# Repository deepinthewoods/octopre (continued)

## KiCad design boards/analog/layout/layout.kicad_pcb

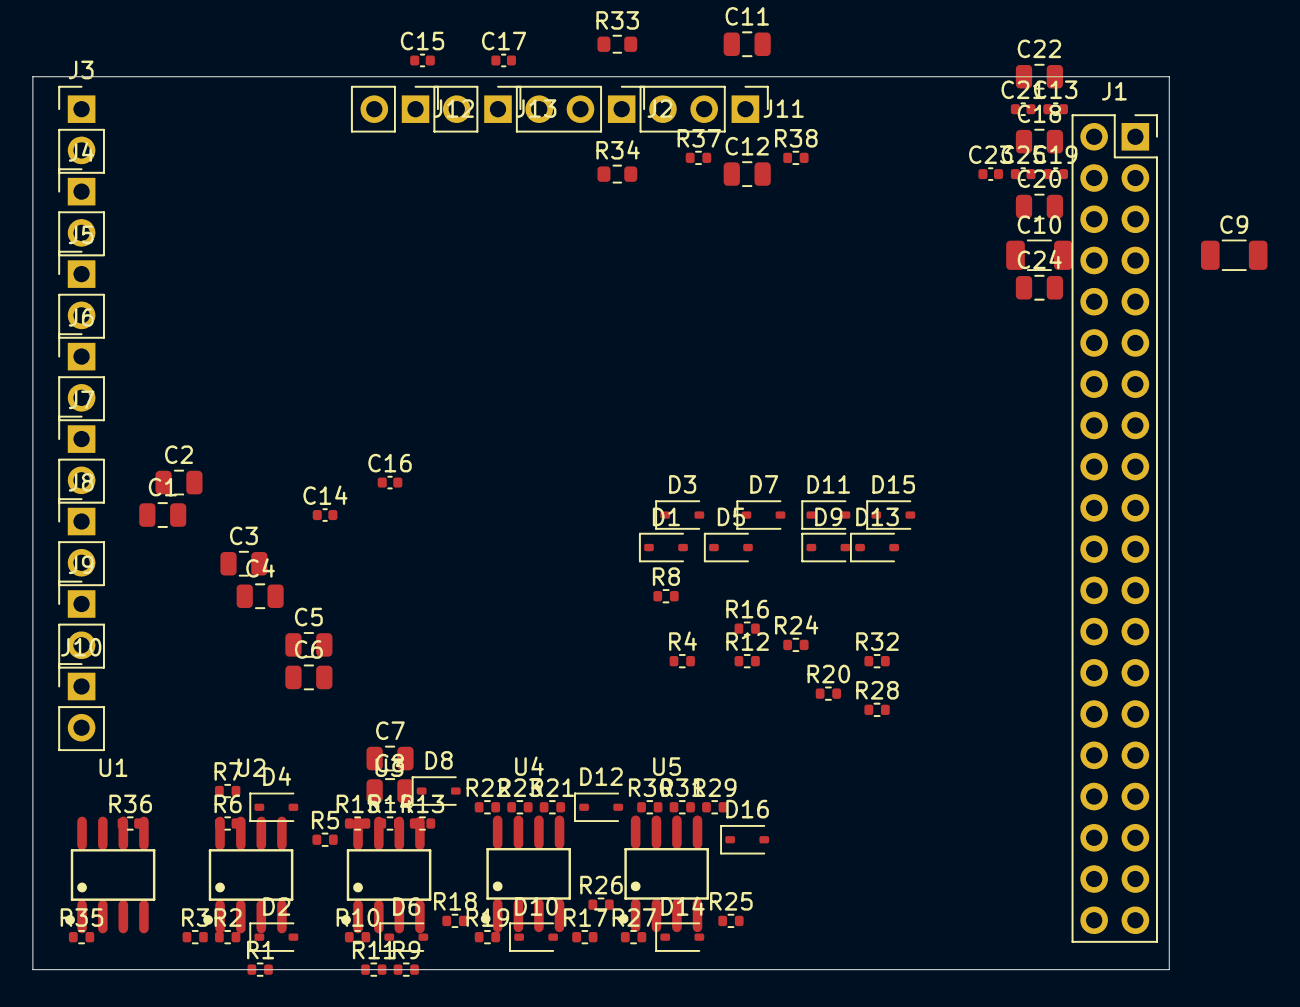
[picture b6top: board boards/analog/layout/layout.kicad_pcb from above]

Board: 6 copper layers, 70.0 x 55.0 mm, 97 parts (0 on the bottom side), 60 nets, no tracks yet.

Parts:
C1, C2, C3, C4, C5, C6, C7, C8, C11, C12, C18, C20, C22, C24: GRM21BZ71E106KE15K; C_0805_2012Metric
C9, C10: 220uF; C_1206_3216Metric
C13, C15, C17, C19, C21, C23, C25: GCM155R71H104KE02D; C_0402_1005Metric
C14, C16: GRM155Z71A105KE01D; C_0402_1005Metric
D1, D2, D3, D4, D5, D6, D7, D8, D9, D10, D11, D12, D13, D14, D15, D16: Schottky; D_SOD-323
J1: 2.54mm 20 x 2 THT Vertical Female; PinSocket_2x20_P2.54mm_Vertical
J2, J11: 61300311121; PinHeader_1x03_P2.54mm_Vertical
J3, J4, J5, J6, J7, J8, J9, J10, J12, J13: 61300211121; PinHeader_1x02_P2.54mm_Vertical
R1, R5, R9, R13, R17, R21, R25, R29: ERJ-2RKF1003X; R_0402_1005Metric
R2, R6, R10, R14, R18, R22, R26, R30: ERJ-2RKF1002X; R_0402_1005Metric
R3, R7, R11, R15, R19, R23, R27, R31: ERJ-2RKF1001X; R_0402_1005Metric
R4, R8, R12, R16, R20, R24, R28, R32: ERJ-2RKF1000X; R_0402_1005Metric
R33, R34: ERJ-H3QF1R0V; R_0603_1608Metric
R35, R36: 600; R_0402_1005Metric
R37, R38: ERJ-2RKF2201X; R_0402_1005Metric
U1, U2, U3, U4, U5: OPA2134UA

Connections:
3V3_ANA: C13.1, C18.1, C19.1, C20.1, C21.1, C22.1, C23.1, C24.1, C25.1, D1.1, D3.1, D5.1, D7.1, D9.1, D11.1, D13.1, D15.1, J1.4, J1.5, R37.1, R38.1, U1.8, U2.8, U3.8, U4.8, U5.8
3V3_DIG: J1.25, J1.26
CH_AC_1: C1.2, C14.2, D1.2, D2.1, R1.1, U2.3
CH_AC_2: C2.2, C16.2, D3.2, D4.1, R5.1, U2.5
CH_AC_3: C3.2, D5.2, D6.1, R9.1, U3.3
CH_AC_4: C4.2, D7.2, D8.1, R13.1, U3.5
CH_AC_5: C5.2, D9.2, D10.1, R17.1, U4.3
CH_AC_6: C6.2, D11.2, D12.1, R21.1, U4.5
CH_AC_7: C7.2, D13.2, D14.1, R25.1, U5.3
CH_AC_8: C8.2, D15.2, D16.1, R29.1, U5.5
CH_FB_1: R2.2, R3.1, U2.2
CH_FB_2: R6.2, R7.1, U2.6
CH_FB_3: R10.2, R11.1, U3.2
CH_FB_4: R14.2, R15.1, U3.6
CH_FB_5: R18.2, R19.1, U4.2
CH_FB_6: R22.2, R23.1, U4.6
CH_FB_7: R26.2, R27.1, U5.2
CH_FB_8: R30.2, R31.1, U5.6
CH_IN_1: C1.1, J3.1
CH_IN_2: C2.1, J4.1
CH_IN_3: C3.1, J5.1
CH_IN_4: C4.1, J6.1
CH_IN_5: C5.1, J7.1
CH_IN_6: C6.1, J8.1
CH_IN_7: C7.1, J9.1
CH_IN_8: C8.1, J10.1
CH_OUT_1: R2.1, R4.1, U2.1
CH_OUT_2: R6.1, R8.1, U2.7
CH_OUT_3: R10.1, R12.1, U3.1
CH_OUT_4: R14.1, R16.1, U3.7
CH_OUT_5: R18.1, R20.1, U4.1
CH_OUT_6: R22.1, R24.1, U4.7
CH_OUT_7: R26.1, R28.1, U5.1
CH_OUT_8: R30.1, R32.1, U5.7
ES_LIN1_2: J1.13, R4.2
ES_LIN1_3: J1.15, R12.2
ES_LIN1_4: J1.17, R20.2
ES_LIN1_5: J1.19, R28.2
ES_RIN1_2: J1.14, R8.2
ES_RIN1_3: J1.16, R16.2
ES_RIN1_4: J1.18, R24.2
ES_RIN1_5: J1.20, R32.2
GND: C13.2, C15.2, C17.2, C18.2, C19.2, C20.2, C21.2, C22.2, C23.2, C24.2, C25.2, D2.2, D4.2, D6.2, D8.2, D10.2, D12.2, D14.2, D16.2, J1.1, J1.2, J1.3, J1.6, J1.23, J1.24, J2.3, J3.2, J4.2, J5.2, J6.2, J7.2, J8.2, J9.2, J10.2, J11.3, J12.2, J13.2, R1.2, R3.2, R5.2, R7.2, R9.2, R11.2, R13.2, R15.2, R17.2, R19.2, R21.2, R23.2, R25.2, R27.2, R29.2, R31.2, U1.4, U2.4, U3.4, U4.4, U5.4
HP_L: C9.1, J1.7
HP_OUT_L: C9.2, R33.1
HP_OUT_R: C10.2, R34.1
HP_PAD_L: J2.1, R33.2
HP_PAD_R: J2.2, R34.2
HP_R: C10.1, J1.8
J_CONN.NC_PH_Pin_40: J1.21, J1.22, J1.27, J1.28, J1.29, J1.30, J1.31, J1.32, J1.33, J1.34, J1.35, J1.36, J1.37, J1.38, J1.39, J1.40
LINE_BUF_L: R35.1, U1.1, U1.2
LINE_BUF_R: R36.1, U1.6, U1.7
LINE_L: J1.9, U1.3
LINE_OUT_L: C11.1, R35.2
LINE_OUT_R: C12.1, R36.2
LINE_PAD_L: C11.2, J11.1
LINE_PAD_R: C12.2, J11.2
LINE_R: J1.10, U1.5
MIC_BIAS_1: C14.1, C15.1, J12.1, R37.2
MIC_BIAS_2: C16.1, C17.1, J13.1, R38.2

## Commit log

2026-03-23 first
2026-03-24 restart
2026-03-24 first of new modular build
2026-03-24 slave subgroup pinouts readdigned
